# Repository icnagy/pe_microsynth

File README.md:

# PE Microsynth / Clef B30

Redrawn in KiCad.

Practical Electronics June 1982
MICROSYNTH Part 1 by A.R. Bradford MSc page 18

Practical Electronics July 1982
MICROSYNTH Part 2 by A.R. Bradford MSc page 38

Practical Electronics August 1982
MICROSYNTH Part 3 by A.R.Bradford MSc page 36

## Schematics

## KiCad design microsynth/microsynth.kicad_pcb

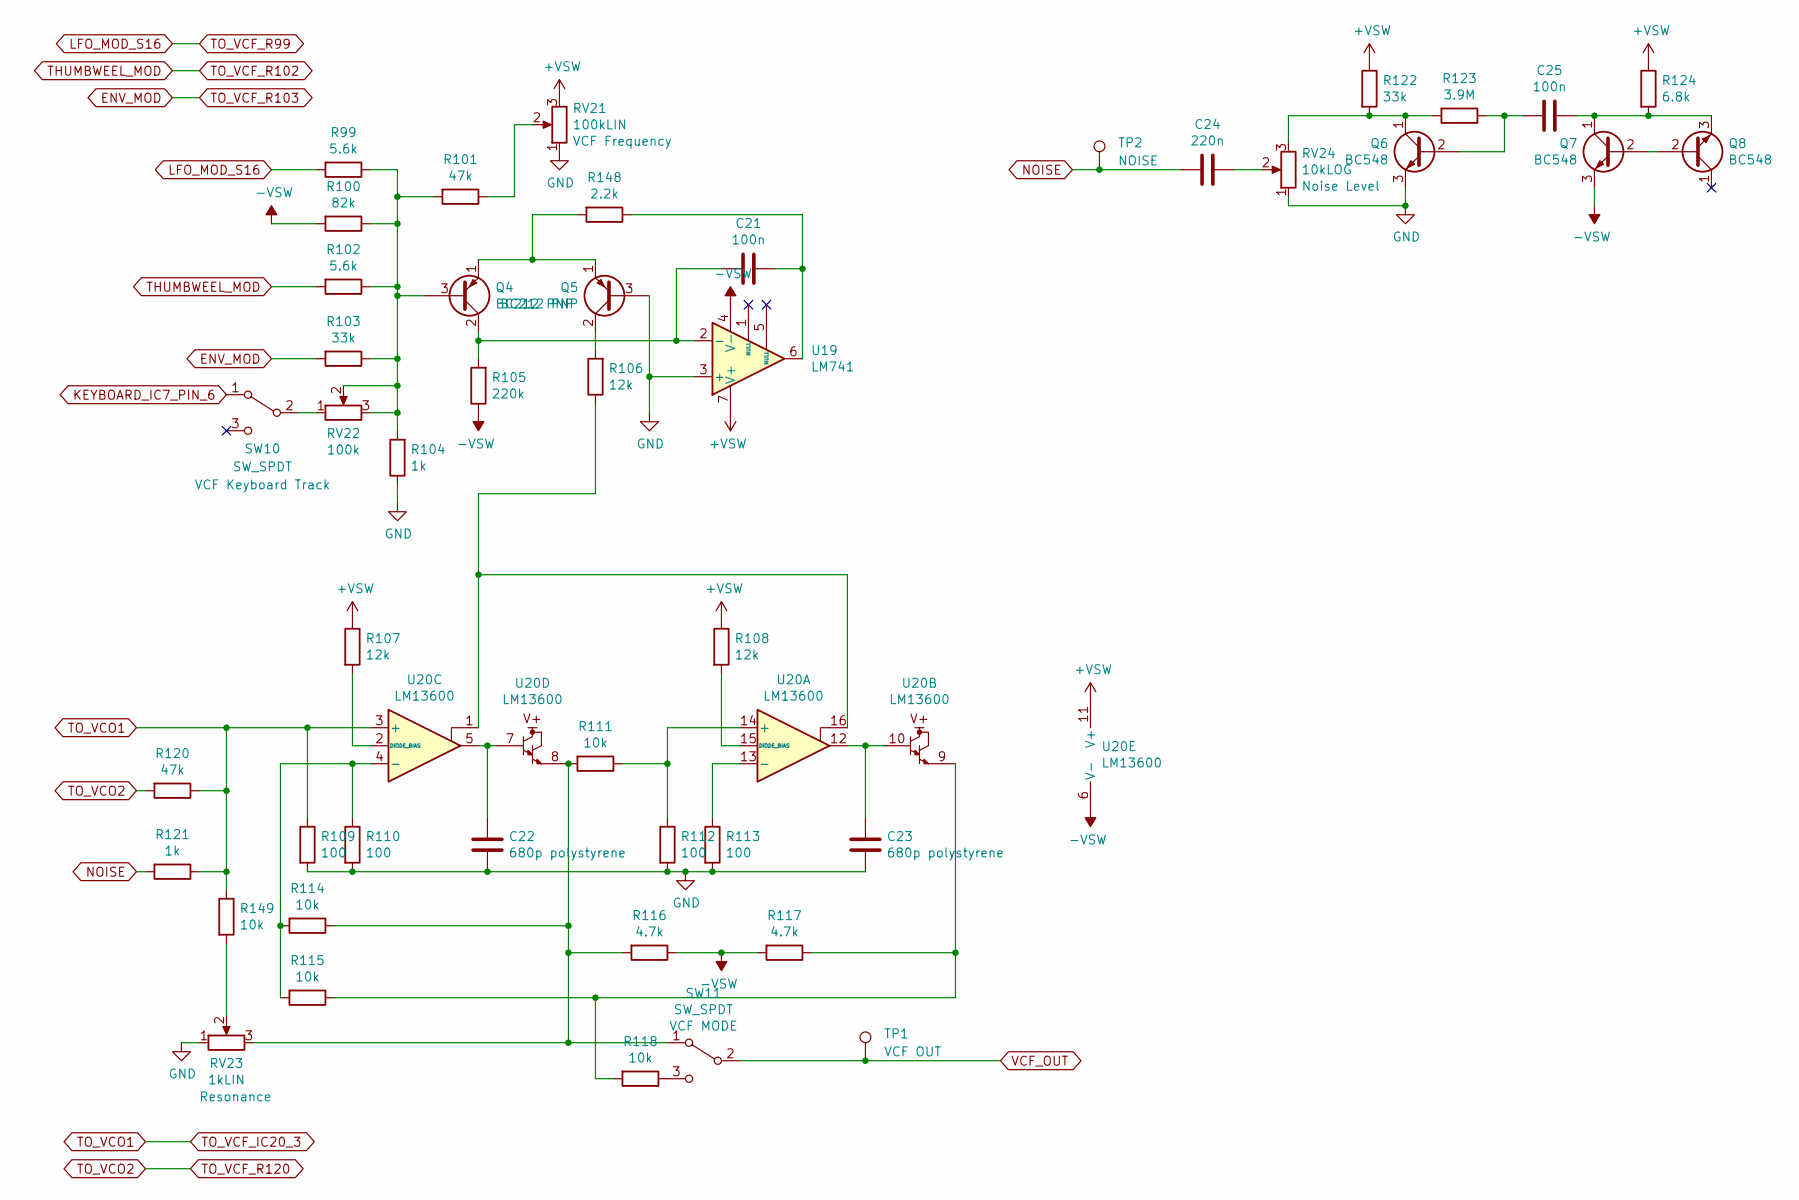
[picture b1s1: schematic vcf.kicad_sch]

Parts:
C21, C25: 100n; C_Rect_L7.2mm_W2.5mm_P5.00mm_FKS2_FKP2_MKS2_MKP2
C22, C23: 680p polystyrene; C_Axial_L12.0mm_D6.5mm_P15.00mm_Horizontal
C24: 220n; C_Rect_L7.2mm_W2.5mm_P5.00mm_FKS2_FKP2_MKS2_MKP2
Q4, Q5: BC212 PNP; TO-92L_Inline_Wide
Q6, Q7, Q8: BC548; TO-92L_Inline_Wide
R99, R102: 5.6k; R_Axial_DIN0207_L6.3mm_D2.5mm_P10.16mm_Horizontal
R100: 82k; R_Axial_DIN0207_L6.3mm_D2.5mm_P10.16mm_Horizontal
R101, R120: 47k; R_Axial_DIN0207_L6.3mm_D2.5mm_P10.16mm_Horizontal
R103, R122: 33k; R_Axial_DIN0207_L6.3mm_D2.5mm_P10.16mm_Horizontal
R104, R121: 1k; R_Axial_DIN0207_L6.3mm_D2.5mm_P10.16mm_Horizontal
R105: 220k; R_Axial_DIN0207_L6.3mm_D2.5mm_P10.16mm_Horizontal
R106, R107, R108: 12k; R_Axial_DIN0207_L6.3mm_D2.5mm_P10.16mm_Horizontal
R109, R110, R112, R113: 100; R_Axial_DIN0207_L6.3mm_D2.5mm_P10.16mm_Horizontal
R111, R114, R115, R118, R149: 10k; R_Axial_DIN0207_L6.3mm_D2.5mm_P10.16mm_Horizontal
R116, R117: 4.7k; R_Axial_DIN0207_L6.3mm_D2.5mm_P10.16mm_Horizontal
R123: 3.9M; R_Axial_DIN0207_L6.3mm_D2.5mm_P10.16mm_Horizontal
R124: 6.8k; R_Axial_DIN0207_L6.3mm_D2.5mm_P10.16mm_Horizontal
R148: 2.2k; R_Axial_DIN0207_L6.3mm_D2.5mm_P10.16mm_Horizontal
RV21: 100kLIN; Pot_16mm_NoDet_RV16AF-4A
RV22: 100k; Potentiometer_Bourns_3296W_Vertical
RV23: 1kLIN; Pot_16mm_NoDet_RV16AF-4A
RV24: 10kLOG; Pot_16mm_NoDet_RV16AF-4A
SW10, SW11: SW_SPDT; 11-SS-22-701C
TP1: VCF OUT; TestPoint_Pad_D2.0mm
TP2: NOISE; TestPoint_Pad_D2.0mm
U19: LM741; DIP-8_W7.62mm_LongPads
U20: LM13600; DIP-16_W7.62mm_LongPads

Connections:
+VSW: R107.1, R108.1, R122.1, R124.1, RV21.3, U19.7 (V+), U20.11 (V+); also elsewhere on the board
-VSW: Q7.3 (E), R100.2, R105.1, R116.1, R117.2, U19.4 (V-), U20.6 (V-); also elsewhere on the board
ENV_MOD: R103.2; also elsewhere on the board
GND: C22.2, C23.2, Q5.3 (B), Q6.3 (E), R104.1, R109.2, R110.2, R112.2, R113.2, RV21.1, RV23.1, RV24.1, U19.3 (+); also elsewhere on the board
KEYBOARD_IC7_PIN_6: SW10.1 (A); also elsewhere on the board
LFO_MOD_S16: R99.2; also elsewhere on the board
NOISE: C24.2, R121.2, TP2.1
unnamed: C21.1, R148.1, U19.6
unnamed: C21.2, Q4.2 (C), R105.2, U19.2 (-)
unnamed: C22.1, U20.5, U20.7
unnamed: C23.1, U20.10, U20.12
unnamed: C24.1, RV24.2
unnamed: C25.1, Q7.1 (C), Q8.3 (E), R124.2
unnamed: C25.2, Q6.2 (B), R123.1
unnamed: Q4.1 (E), Q5.1 (E), R148.2
unnamed: Q4.3 (B), R99.1, R100.1, R101.2, R102.1, R103.1, R104.2, RV22.2, RV22.3
unnamed: Q5.2 (C), R106.2
unnamed: Q6.1 (C), R122.2, R123.2, RV24.3
unnamed: Q7.2 (B), Q8.2 (B)
unnamed: R101.1, RV21.2
unnamed: R106.1, U20.1, U20.16
unnamed: R107.2, U20.2 (DIODE_BIAS)
unnamed: R108.2, U20.15 (DIODE_BIAS)
unnamed: R110.1, R114.2, R115.2, U20.4 (-)
unnamed: R111.1, R112.1, U20.14 (+)
unnamed: R111.2, R114.1, R116.2, RV23.3, SW11.1 (A), U20.8
unnamed: R113.1, U20.13 (-)
unnamed: R115.1, R117.1, R118.2, U20.9
unnamed: R118.1, SW11.3 (C)
unnamed: R149.2, RV23.2
unnamed: RV22.1, SW10.2 (B)
THUMBWEEL_MOD: R102.2; also elsewhere on the board
TO_VCF_IC20_3: R109.1, R120.1, R121.1, R149.1, U20.3 (+); also elsewhere on the board
TO_VCF_R120: R120.2; also elsewhere on the board
VCF_OUT: SW11.2 (B), TP1.1; also elsewhere on the board

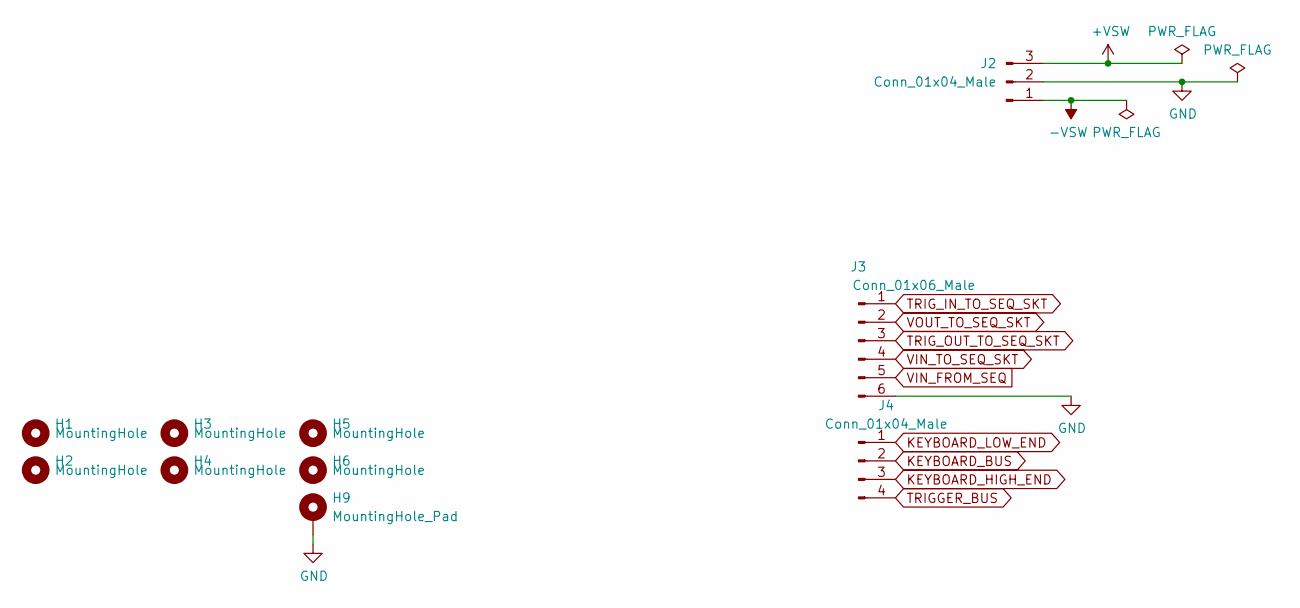
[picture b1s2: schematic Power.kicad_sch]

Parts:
H1, H2, H3, H4, H5, H6: MountingHole; MountingHole_3.2mm_M3
H9: MountingHole_Pad; PinHeader_1x01_P2.54mm_Vertical
J2: Conn_01x04_Male; PhoenixContact_MSTBA_2,5_3-G_1x03_P5.00mm_Horizontal
J3: Conn_01x06_Male; PinHeader_1x06_P2.54mm_Vertical
J4: Conn_01x04_Male; PinHeader_1x04_P2.54mm_Vertical

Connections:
+VSW: J2.3; also elsewhere on the board
-VSW: J2.1; also elsewhere on the board
GND: H9.1, J2.2, J3.6; also elsewhere on the board
KEYBOARD_BUS: J4.2; also elsewhere on the board
KEYBOARD_HIGH_END: J4.3; also elsewhere on the board
KEYBOARD_LOW_END: J4.1; also elsewhere on the board
TRIGGER_BUS: J4.4; also elsewhere on the board
TRIG_IN_TO_SEQ_SKT: J3.1; also elsewhere on the board
TRIG_OUT_TO_SEQ_SKT: J3.3; also elsewhere on the board
VIN_FROM_SEQ: J3.5; also elsewhere on the board
VIN_TO_SEQ_SKT: J3.4; also elsewhere on the board
VOUT_TO_SEQ_SKT: J3.2; also elsewhere on the board

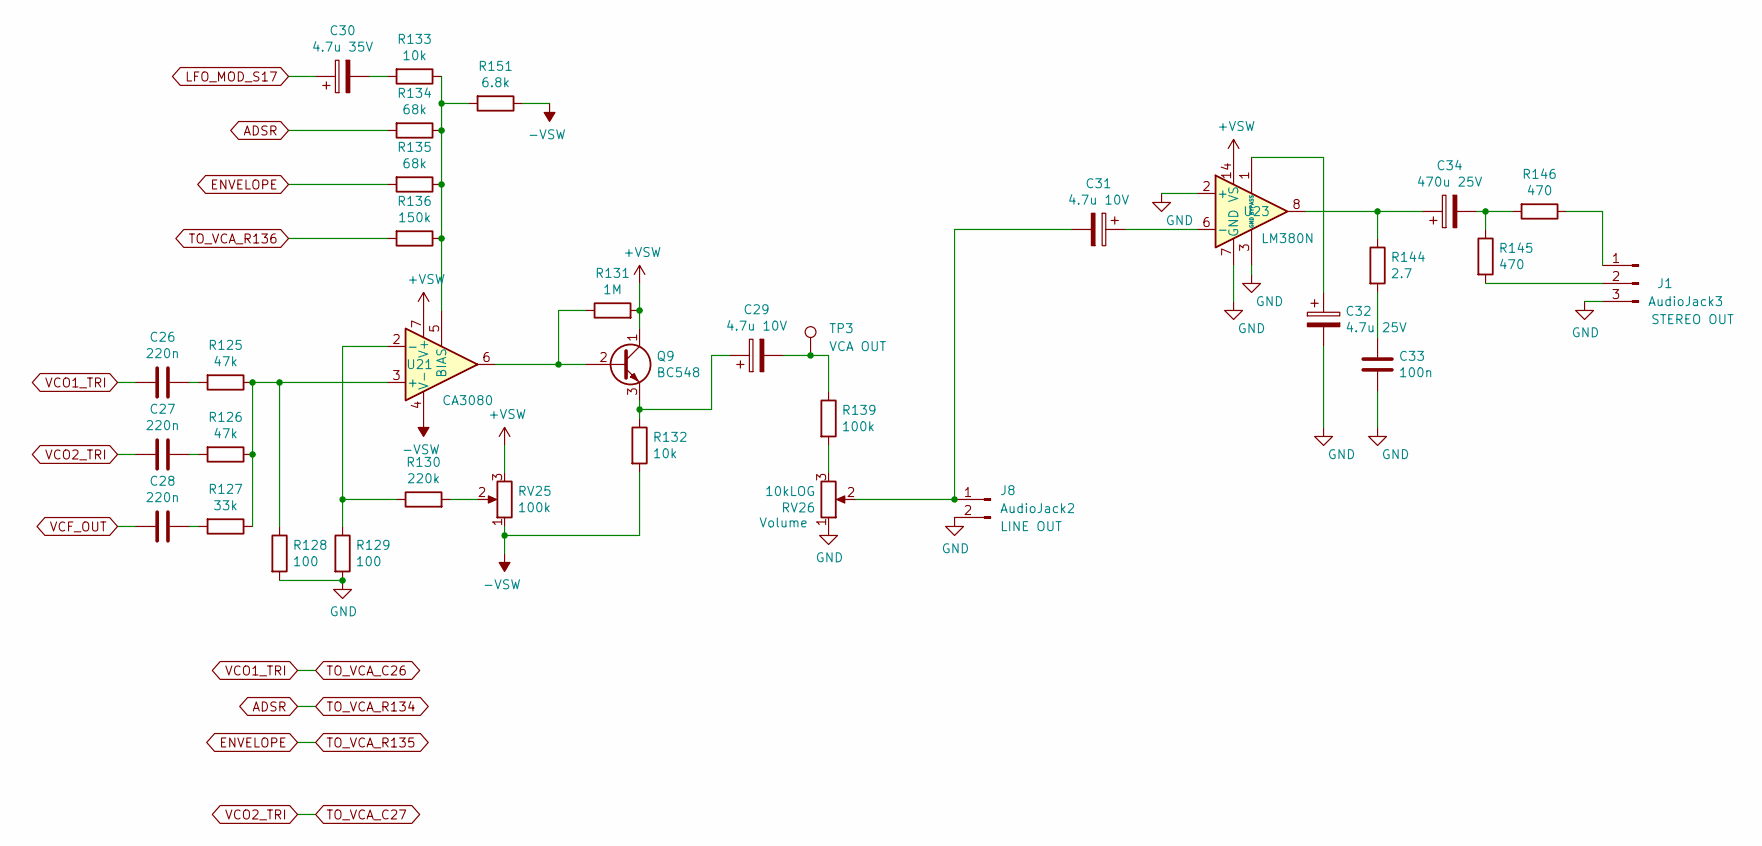
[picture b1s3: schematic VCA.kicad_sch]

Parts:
C26, C27, C28: 220n; C_Rect_L7.2mm_W2.5mm_P5.00mm_FKS2_FKP2_MKS2_MKP2
C29, C31: 4.7u 10V; CP_Radial_D5.0mm_P2.50mm
C30: 4.7u 35V; CP_Radial_D5.0mm_P2.50mm
C32: 4.7u 25V; CP_Radial_D5.0mm_P2.50mm
C33: 100n; C_Rect_L7.2mm_W2.5mm_P5.00mm_FKS2_FKP2_MKS2_MKP2
C34: 470u 25V; CP_Radial_D10.0mm_P5.00mm
J1: AudioJack3; PinHeader_1x03_P2.54mm_Vertical
J8: AudioJack2; PinHeader_1x02_P2.54mm_Vertical
Q9: BC548; TO-92L_Inline_Wide
R125, R126: 47k; R_Axial_DIN0207_L6.3mm_D2.5mm_P10.16mm_Horizontal
R127: 33k; R_Axial_DIN0207_L6.3mm_D2.5mm_P10.16mm_Horizontal
R128, R129: 100; R_Axial_DIN0207_L6.3mm_D2.5mm_P10.16mm_Horizontal
R130: 220k; R_Axial_DIN0207_L6.3mm_D2.5mm_P10.16mm_Horizontal
R131: 1M; R_Axial_DIN0207_L6.3mm_D2.5mm_P10.16mm_Horizontal
R132, R133: 10k; R_Axial_DIN0207_L6.3mm_D2.5mm_P10.16mm_Horizontal
R134, R135: 68k; R_Axial_DIN0207_L6.3mm_D2.5mm_P10.16mm_Horizontal
R136: 150k; R_Axial_DIN0207_L6.3mm_D2.5mm_P10.16mm_Horizontal
R139: 100k; R_Axial_DIN0207_L6.3mm_D2.5mm_P10.16mm_Horizontal
R144: 2.7; R_Axial_DIN0207_L6.3mm_D2.5mm_P10.16mm_Horizontal
R145, R146: 470; R_Axial_DIN0207_L6.3mm_D2.5mm_P10.16mm_Horizontal
R151: 6.8k; R_Axial_DIN0207_L6.3mm_D2.5mm_P10.16mm_Horizontal
RV25: 100k; Potentiometer_Bourns_3296W_Vertical
RV26: 10kLOG; PinHeader_1x03_P2.54mm_Vertical
TP3: VCA OUT; TestPoint_Pad_D2.0mm
U21: CA3080; DIP-8_W7.62mm_LongPads
U23: LM380N; DIP-14_W7.62mm_LongPads

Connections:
+VSW: Q9.1 (C), R131.2, RV25.3, U21.7 (V+), U23.14 (VS); also elsewhere on the board
-VSW: R132.2, R151.1, RV25.1, U21.4 (V-); also elsewhere on the board
ADSR: R134.2; also elsewhere on the board
ENVELOPE: R135.2; also elsewhere on the board
GND: C32.2, C33.2, J1.3, J8.2, R128.2, R129.2, RV26.1, U23.2 (+), U23.3 (GND), U23.4 (GND), U23.5 (GND), U23.7 (GND), U23.10 (GND), U23.11 (GND), U23.12 (GND); also elsewhere on the board
LFO_MOD_S17: C30.1; also elsewhere on the board
unnamed: C26.1, R125.2
unnamed: C27.2, R126.2
unnamed: C28.2, R127.2
unnamed: C29.1, Q9.3 (E), R132.1
unnamed: C29.2, R139.1, TP3.1
unnamed: C30.2, R133.2
unnamed: C31.1, U23.6 (-)
unnamed: C31.2, J8.1, RV26.2
unnamed: C32.1, U23.1 (BYPASS)
unnamed: C33.1, R144.2
unnamed: C34.1, R144.1, U23.8
unnamed: C34.2, R145.1, R146.2
unnamed: J1.1, R146.1
unnamed: J1.2, R145.2
unnamed: Q9.2 (B), R131.1, U21.6
unnamed: R125.1, R126.1, R127.1, R128.1, U21.3 (+)
unnamed: R129.1, R130.1, U21.2 (-)
unnamed: R130.2, RV25.2
unnamed: R133.1, R134.1, R135.1, R136.1, R151.2, U21.5 (BIAS)
unnamed: R139.2, RV26.3
TO_VCA_C26: C26.2; also elsewhere on the board
TO_VCA_C27: C27.1; also elsewhere on the board
TO_VCA_R136: R136.2; also elsewhere on the board
VCF_OUT: C28.1; also elsewhere on the board

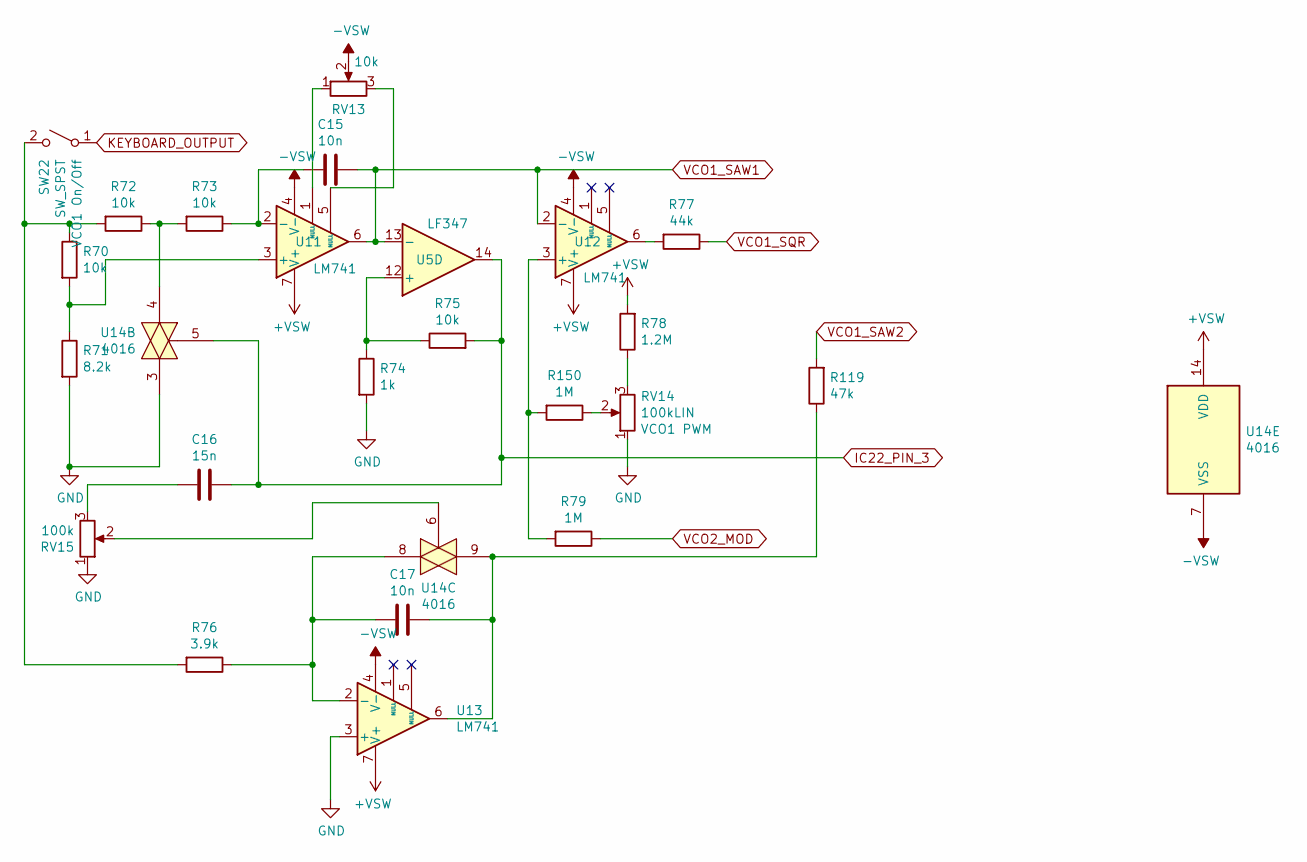
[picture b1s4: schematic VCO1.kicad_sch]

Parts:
C15, C17: 10n; C_Rect_L7.2mm_W2.5mm_P5.00mm_FKS2_FKP2_MKS2_MKP2
C16: 15n; C_Rect_L7.2mm_W3.5mm_P5.00mm_FKS2_FKP2_MKS2_MKP2
R70, R72, R73, R75: 10k; R_Axial_DIN0207_L6.3mm_D2.5mm_P10.16mm_Horizontal
R71: 8.2k; R_Axial_DIN0207_L6.3mm_D2.5mm_P10.16mm_Horizontal
R74: 1k; R_Axial_DIN0207_L6.3mm_D2.5mm_P10.16mm_Horizontal
R76: 3.9k; R_Axial_DIN0207_L6.3mm_D2.5mm_P10.16mm_Horizontal
R77: 44k; R_Axial_DIN0207_L6.3mm_D2.5mm_P10.16mm_Horizontal
R78: 1.2M; R_Axial_DIN0207_L6.3mm_D2.5mm_P10.16mm_Horizontal
R79, R150: 1M; R_Axial_DIN0207_L6.3mm_D2.5mm_P10.16mm_Horizontal
R119: 47k; R_Axial_DIN0207_L6.3mm_D2.5mm_P10.16mm_Horizontal
RV13: 10k; Potentiometer_Bourns_3296W_Vertical
RV14: 100kLIN; Pot_16mm_NoDet_RV16AF-4A
RV15: 100k; Potentiometer_Bourns_3296W_Vertical
SW22: SW_SPST; SPDT_KIT
U5: LF347; DIP-14_W7.62mm_LongPads
U11, U12, U13: LM741; DIP-8_W7.62mm_LongPads
U14: 4016; DIP-14_W7.62mm_LongPads

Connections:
+VSW: R78.2, U11.7 (V+), U12.7 (V+), U13.7 (V+), U14.14 (VDD); also elsewhere on the board
-VSW: RV13.2, U11.4 (V-), U12.4 (V-), U13.4 (V-), U14.7 (VSS); also elsewhere on the board
GND: R71.2, R74.2, RV14.1, RV15.1, U13.3 (+), U14.3; also elsewhere on the board
IC22_PIN_3: C16.1, R75.2, U5.14, U14.5; also elsewhere on the board
KEYBOARD_IC7_PIN_6: SW22.1 (A); also elsewhere on the board
unnamed: C15.2, R73.1, U11.2 (-)
unnamed: C16.2, RV15.3
unnamed: C17.1, R119.1, U13.6, U14.9
unnamed: C17.2, R76.1, U13.2 (-), U14.8
unnamed: R70.1, R72.2, R76.2, SW22.2 (B)
unnamed: R70.2, R71.1, U11.3 (+)
unnamed: R72.1, R73.2, U14.4
unnamed: R74.1, R75.1, U5.12 (+)
unnamed: R77.2, U12.6
unnamed: R78.1, RV14.3
unnamed: R150.1, RV14.2
unnamed: R79.2, R150.2, U12.3 (+)
unnamed: RV13.1, U11.1 (NULL)
unnamed: RV13.3, U11.5 (NULL)
unnamed: RV15.2, U14.6
TO_VCO1_R79: R79.1; also elsewhere on the board
VCO1_SAW1: C15.1, U5.13 (-), U11.6, U12.2 (-); also elsewhere on the board
VCO1_SAW2: R119.2; also elsewhere on the board
VCO1_SQR: R77.1; also elsewhere on the board

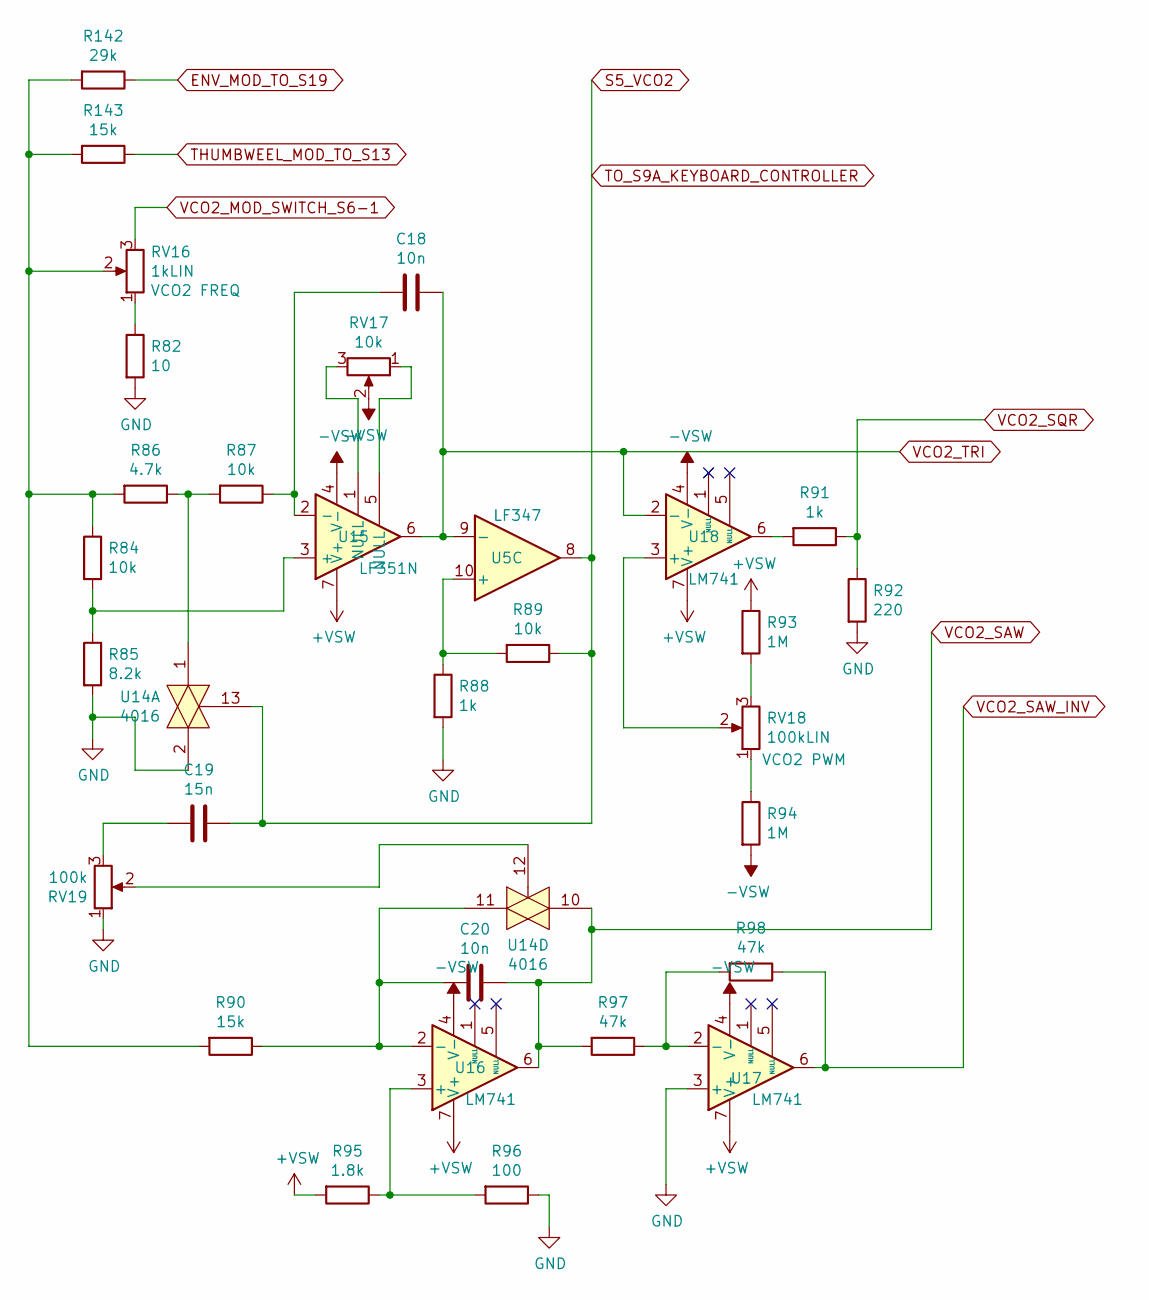
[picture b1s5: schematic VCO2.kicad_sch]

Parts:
C18, C20: 10n; C_Rect_L7.2mm_W2.5mm_P5.00mm_FKS2_FKP2_MKS2_MKP2
C19: 15n; C_Rect_L7.2mm_W3.5mm_P5.00mm_FKS2_FKP2_MKS2_MKP2
R82: 10; R_Axial_DIN0207_L6.3mm_D2.5mm_P10.16mm_Horizontal
R84, R87, R89: 10k; R_Axial_DIN0207_L6.3mm_D2.5mm_P10.16mm_Horizontal
R85: 8.2k; R_Axial_DIN0207_L6.3mm_D2.5mm_P10.16mm_Horizontal
R86: 4.7k; R_Axial_DIN0207_L6.3mm_D2.5mm_P10.16mm_Horizontal
R88, R91: 1k; R_Axial_DIN0207_L6.3mm_D2.5mm_P10.16mm_Horizontal
R90, R143: 15k; R_Axial_DIN0207_L6.3mm_D2.5mm_P10.16mm_Horizontal
R92: 220; R_Axial_DIN0207_L6.3mm_D2.5mm_P10.16mm_Horizontal
R93, R94: 1M; R_Axial_DIN0207_L6.3mm_D2.5mm_P10.16mm_Horizontal
R95: 1.8k; R_Axial_DIN0207_L6.3mm_D2.5mm_P10.16mm_Horizontal
R96: 100; R_Axial_DIN0207_L6.3mm_D2.5mm_P10.16mm_Horizontal
R97, R98: 47k; R_Axial_DIN0207_L6.3mm_D2.5mm_P10.16mm_Horizontal
R142: 29k; R_Axial_DIN0207_L6.3mm_D2.5mm_P10.16mm_Horizontal
RV16: 1kLIN; Pot_16mm_NoDet_RV16AF-4A
RV17: 10k; Potentiometer_Bourns_3296W_Vertical
RV18: 100kLIN; Pot_16mm_NoDet_RV16AF-4A
RV19: 100k; Potentiometer_Bourns_3296W_Vertical
U5: LF347; DIP-14_W7.62mm_LongPads
U14: 4016; DIP-14_W7.62mm_LongPads
U15: LF351N; DIP-8_W7.62mm_LongPads
U16, U17, U18: LM741; DIP-8_W7.62mm_LongPads

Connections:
+VSW: R93.1, R95.2, U15.7 (V+), U16.7 (V+), U17.7 (V+), U18.7 (V+); also elsewhere on the board
-VSW: R94.2, RV17.2, U15.4 (V-), U16.4 (V-), U17.4 (V-), U18.4 (V-); also elsewhere on the board
ENV_MOD_TO_S19: R142.1; also elsewhere on the board
GND: R82.2, R85.2, R88.2, R92.2, R96.1, RV19.1, U14.2, U17.3 (+); also elsewhere on the board
unnamed: C18.2, R87.1, U15.2 (-)
unnamed: C19.2, RV19.3
unnamed: C20.2, R90.1, U14.11, U16.2 (-)
unnamed: R82.1, RV16.1
unnamed: R84.2, R85.1, U15.3 (+)
unnamed: R86.1, R87.2, U14.1
unnamed: R88.1, R89.2, U5.10 (+)
unnamed: R91.2, U18.6
unnamed: R93.2, RV18.3
unnamed: R94.1, RV18.1
unnamed: R95.1, R96.2, U16.3 (+)
unnamed: R97.1, R98.2, U17.2 (-)
unnamed: R84.1, R86.2, R90.2, R142.2, R143.2, RV16.2
unnamed: RV17.1, U15.5 (NULL)
unnamed: RV17.3, U15.1 (NULL)
unnamed: RV18.2, U18.3 (+)
unnamed: RV19.2, U14.12
S5_VCO2: C19.1, R89.1, U5.8, U14.13; also elsewhere on the board
THUMBWEEL_MOD_TO_S13: R143.1; also elsewhere on the board
TO_VCA_C27: C18.1, U5.9 (-), U15.6, U18.2 (-); also elsewhere on the board
VCO2_MOD_SWITCH_S6-1: RV16.3; also elsewhere on the board
VCO2_SAW: C20.1, R97.2, U14.10, U16.6; also elsewhere on the board
VCO2_SAW_INV: R98.1, U17.6; also elsewhere on the board
VCO2_SQR: R91.1, R92.1; also elsewhere on the board

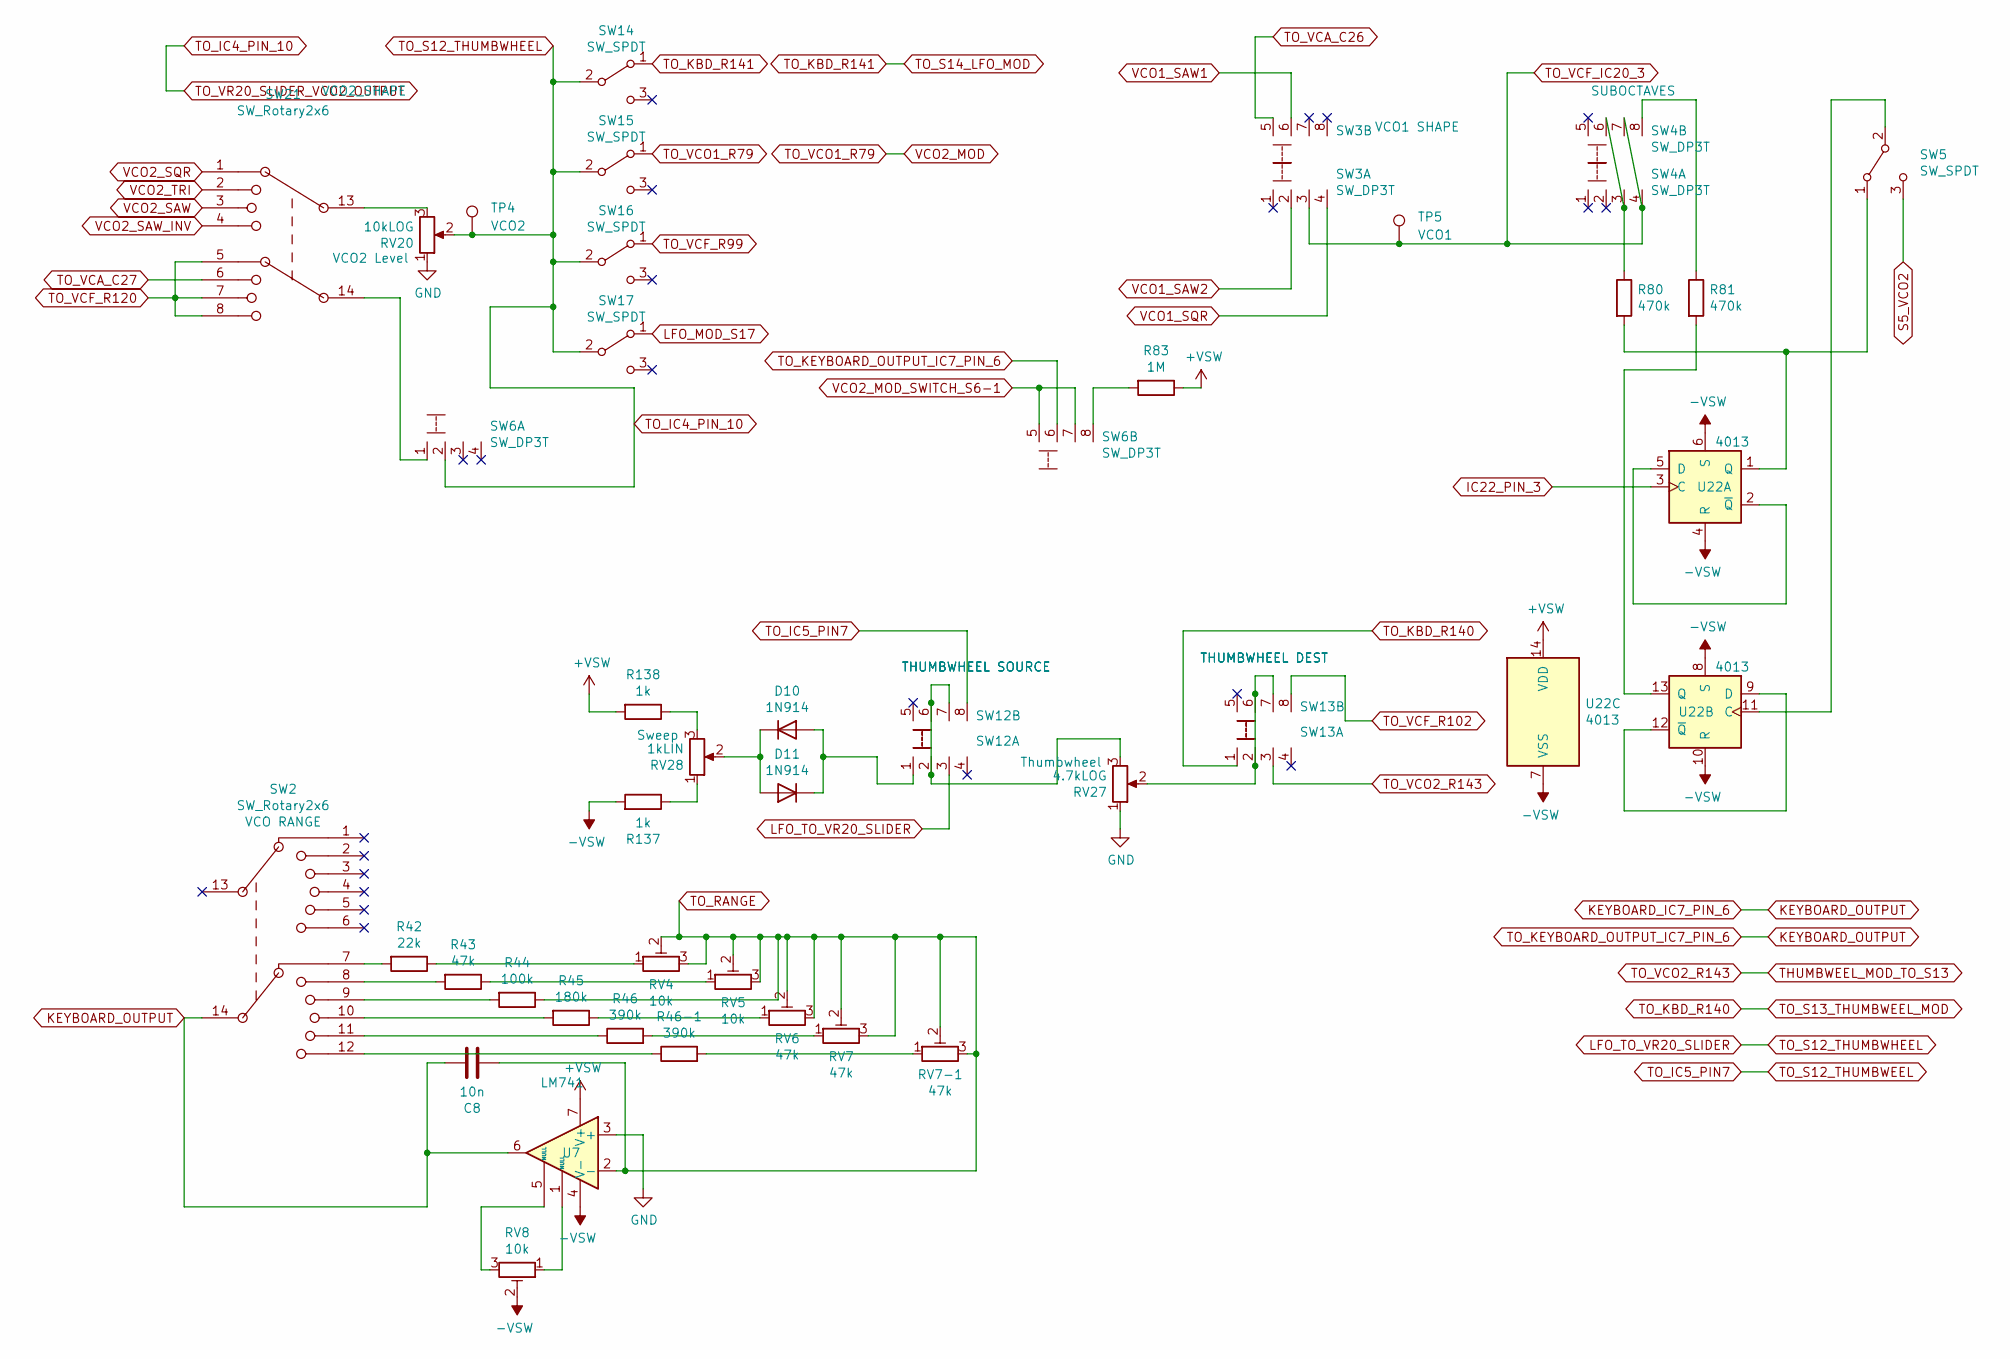
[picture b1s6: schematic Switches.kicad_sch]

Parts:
C8: 10n; C_Rect_L7.2mm_W2.5mm_P5.00mm_FKS2_FKP2_MKS2_MKP2
D10, D11: 1N914; D_DO-35_SOD27_P7.62mm_Horizontal
R42: 22k; R_Axial_DIN0207_L6.3mm_D2.5mm_P10.16mm_Horizontal
R43: 47k; R_Axial_DIN0207_L6.3mm_D2.5mm_P10.16mm_Horizontal
R44: 100k; R_Axial_DIN0207_L6.3mm_D2.5mm_P10.16mm_Horizontal
R45: 180k; R_Axial_DIN0207_L6.3mm_D2.5mm_P10.16mm_Horizontal
R46, R46-1: 390k; R_Axial_DIN0207_L6.3mm_D2.5mm_P10.16mm_Horizontal
R80, R81: 470k; R_Axial_DIN0207_L6.3mm_D2.5mm_P10.16mm_Horizontal
R83: 1M; R_Axial_DIN0207_L6.3mm_D2.5mm_P10.16mm_Horizontal
R137, R138: 1k; R_Axial_DIN0207_L6.3mm_D2.5mm_P10.16mm_Horizontal
RV4, RV5, RV8: 10k; Potentiometer_Bourns_3296W_Vertical
RV6, RV7, RV7-1: 47k; Potentiometer_Bourns_3296W_Vertical
RV20: 10kLOG; Pot_16mm_NoDet_RV16AF-4A
RV27: 4.7kLOG; Potentiometer_Bourns_PTV09A-2_Vertical
RV28: 1kLIN; Pot_16mm_NoDet_RV16AF-4A
SW2: SW_Rotary2x6; SR2511F-0206-(L)K0A-C9-S-3
SW3, SW4, SW6: SW_DP3T; 11-SS-23-832C
SW5, SW14, SW15, SW16, SW17: SW_SPDT; 11-SS-22-701C
SW12: THUMBWHEEL SOURCE; 11-SS-23-832C
SW13: THUMBWHEEL DEST; 11-SS-23-832C
SW21: SW_Rotary2x6; SR2511F-0204-(L)K0A-C9-S-3
TP4: VCO2; TestPoint_Pad_D2.0mm
TP5: VCO1; TestPoint_Pad_D2.0mm
U7: LM741; DIP-8_W7.62mm_LongPads
U22: 4013; DIP-14_W7.62mm_LongPads

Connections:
+VSW: R83.1, R138.2, U7.7 (V+), U22.14 (VDD); also elsewhere on the board
-VSW: R137.2, RV8.2, U7.4 (V-), U22.4 (R), U22.6 (S), U22.7 (VSS), U22.8 (S), U22.10 (R); also elsewhere on the board
GND: RV20.1, RV27.1, U7.3 (+); also elsewhere on the board
IC22_PIN_3: U22.3 (C); also elsewhere on the board
KEYBOARD_IC7_PIN_6: C8.1, SW2.14, SW6.6, U7.6; also elsewhere on the board
LFO_MOD_S16: SW16.1 (A); also elsewhere on the board
LFO_MOD_S17: SW17.1 (A); also elsewhere on the board
LFO_TO_VR20_SLIDER: RV20.2, SW6.2, SW12.3, SW14.2 (B), SW15.2 (B), SW16.2 (B), SW17.2 (B), TP4.1; also elsewhere on the board
unnamed: D10.1 (K), D11.2 (A), RV28.2
unnamed: D10.2 (A), D11.1 (K), SW12.1
unnamed: R42.1, RV4.1
unnamed: R42.2, SW2.7
unnamed: R43.1, RV5.1
unnamed: R43.2, SW2.8
unnamed: R44.2, SW2.9
unnamed: R45.1, RV6.1
unnamed: R45.2, SW2.10
unnamed: R46-1.1, SW2.12
unnamed: R46-1.2, RV7-1.1
unnamed: R46.1, SW2.11
unnamed: R46.2, RV7.1
unnamed: R80.1, SW4.3, SW4.6
unnamed: R80.2, SW5.1 (A), U22.1 (Q)
unnamed: R81.1, SW4.8
unnamed: R81.2, U22.13 (Q)
unnamed: R83.2, SW6.8
unnamed: R137.1, RV28.1
unnamed: R138.1, RV28.3
unnamed: RV8.1, U7.1 (NULL)
unnamed: RV8.3, U7.5 (NULL)
unnamed: RV20.3, SW21.13
unnamed: RV27.2, SW13.2, SW13.6, SW13.7
unnamed: RV27.3, SW12.2, SW12.6, SW12.7
unnamed: SW5.2 (B), U22.11 (C)
unnamed: SW6.1, SW21.14
unnamed: U22.2 (~Q), U22.5 (D)
unnamed: U22.9 (D), U22.12 (~Q)
S5_VCO2: SW5.3 (C); also elsewhere on the board
THUMBWEEL_MOD: SW13.8; also elsewhere on the board
THUMBWEEL_MOD_TO_S13: SW13.3; also elsewhere on the board
TO_IC5_PIN7: SW12.8; also elsewhere on the board
TO_KBD_R140: SW13.1; also elsewhere on the board
TO_KBD_R141: SW14.1 (A); also elsewhere on the board
TO_RANGE: C8.2, R44.1, RV4.2, RV4.3, RV5.2, RV5.3, RV6.2, RV6.3, RV7.2, RV7.3, RV7-1.2, RV7-1.3, U7.2 (-); also elsewhere on the board
TO_VCA_C26: SW3.5; also elsewhere on the board
TO_VCA_C27: SW21.2, SW21.6; also elsewhere on the board
TO_VCF_IC20_3: SW3.3, SW4.4, SW4.7, TP5.1; also elsewhere on the board
TO_VCF_R120: SW21.5, SW21.7, SW21.8; also elsewhere on the board
TO_VCO1_R79: SW15.1 (A); also elsewhere on the board
VCO1_SAW1: SW3.6; also elsewhere on the board
VCO1_SAW2: SW3.2; also elsewhere on the board
VCO1_SQR: SW3.4; also elsewhere on the board
VCO2_MOD_SWITCH_S6-1: SW6.5, SW6.7; also elsewhere on the board
VCO2_SAW: SW21.3; also elsewhere on the board
VCO2_SAW_INV: SW21.4; also elsewhere on the board
VCO2_SQR: SW21.1; also elsewhere on the board

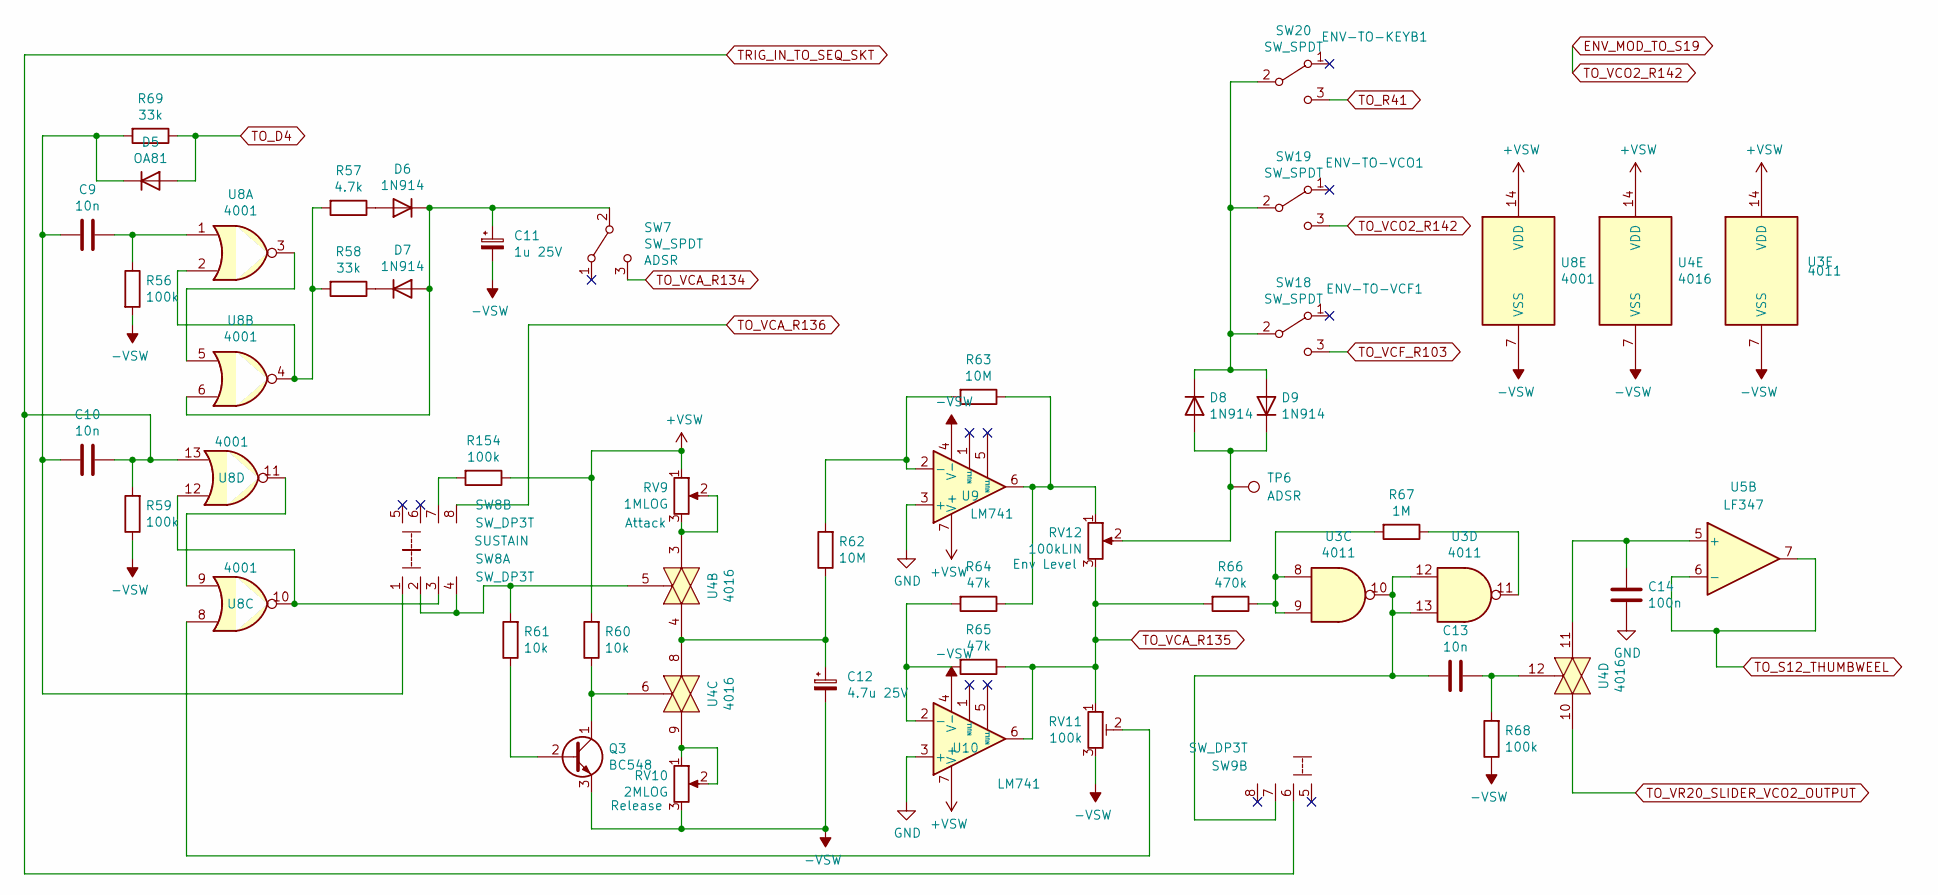
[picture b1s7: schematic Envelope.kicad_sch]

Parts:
C9, C10, C13: 10n; C_Rect_L7.2mm_W2.5mm_P5.00mm_FKS2_FKP2_MKS2_MKP2
C11: 1u 25V; CP_Radial_D5.0mm_P2.50mm
C12: 4.7u 25V; CP_Radial_D5.0mm_P2.50mm
C14: 100n; C_Rect_L7.2mm_W2.5mm_P5.00mm_FKS2_FKP2_MKS2_MKP2
D5: OA81; D_A-405_P10.16mm_Horizontal
D6, D7, D8, D9: 1N914; D_DO-35_SOD27_P7.62mm_Horizontal
Q3: BC548; TO-92L_Inline_Wide
R56, R59, R68, R154: 100k; R_Axial_DIN0207_L6.3mm_D2.5mm_P10.16mm_Horizontal
R57: 4.7k; R_Axial_DIN0207_L6.3mm_D2.5mm_P10.16mm_Horizontal
R58, R69: 33k; R_Axial_DIN0207_L6.3mm_D2.5mm_P10.16mm_Horizontal
R60, R61: 10k; R_Axial_DIN0207_L6.3mm_D2.5mm_P10.16mm_Horizontal
R62, R63: 10M; R_Axial_DIN0207_L6.3mm_D2.5mm_P10.16mm_Horizontal
R64, R65: 47k; R_Axial_DIN0207_L6.3mm_D2.5mm_P10.16mm_Horizontal
R66: 470k; R_Axial_DIN0207_L6.3mm_D2.5mm_P10.16mm_Horizontal
R67: 1M; R_Axial_DIN0207_L6.3mm_D2.5mm_P10.16mm_Horizontal
RV9: 1MLOG; Pot_16mm_NoDet_RV16AF-4A
RV10: 2MLOG; Pot_16mm_NoDet_RV16AF-4A
RV11: 100k; Potentiometer_Bourns_3296W_Vertical
RV12: 100kLIN; Pot_16mm_NoDet_RV16AF-4A
SW7, SW18, SW19, SW20: SW_SPDT; 11-SS-22-701C
SW8, SW9: SW_DP3T; 11-SS-23-832C
TP6: ADSR; TestPoint_Pad_D2.0mm
U3: 4011; DIP-14_W7.62mm_LongPads
U4: 4016; DIP-14_W7.62mm_LongPads
U5: LF347; DIP-14_W7.62mm_LongPads
U8: 4001; DIP-14_W7.62mm_LongPads
U9, U10: LM741; DIP-8_W7.62mm_LongPads

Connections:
+VSW: R60.2, R154.1, RV9.1, U3.14 (VDD), U4.14 (VDD), U8.14 (VDD), U9.7 (V+), U10.7 (V+); also elsewhere on the board
-VSW: C11.2, C12.2, Q3.3 (E), R56.2, R59.1, R68.1, RV10.3, RV11.3, U3.7 (VSS), U4.7 (VSS), U8.7 (VSS), U9.4 (V-), U10.4 (V-); also elsewhere on the board
ADSR: SW7.3 (C); also elsewhere on the board
ENVELOPE: R65.1, R66.2, RV11.1, RV12.3, U10.6; also elsewhere on the board
ENV_MOD: SW18.3 (C); also elsewhere on the board
ENV_MOD_TO_S19: SW19.3 (C); also elsewhere on the board
GND: C14.2, U9.3 (+), U10.3 (+); also elsewhere on the board
LFO_TO_VR20_SLIDER: U4.10; also elsewhere on the board
unnamed: C9.1, R56.1, U8.1
unnamed: C9.2, C10.2, D5.1 (K), R69.2, SW8.1
unnamed: C11.1, D6.1 (K), D7.2 (A), SW7.2 (B), U8.6
unnamed: C12.1, R62.1, U4.4, U4.8
unnamed: C13.1, R68.2, U4.12
unnamed: C13.2, SW9.7, U3.10, U3.12, U3.13
unnamed: C14.1, U4.11, U5.5 (+)
unnamed: D6.2 (A), R57.1
unnamed: D7.1 (K), R58.1
unnamed: D8.1 (K), D9.2 (A), SW18.2 (B), SW19.2 (B), SW20.2 (B)
unnamed: D8.2 (A), D9.1 (K), RV12.2, TP6.1
unnamed: Q3.1 (C), R60.1, U4.6
unnamed: Q3.2 (B), R61.1
unnamed: R57.2, R58.2, U8.2, U8.4
unnamed: R61.2, SW8.2, SW8.4, U4.5
unnamed: R62.2, R63.2, U9.2 (-)
unnamed: R63.1, R64.1, RV12.1, U9.6
unnamed: R64.2, R65.2, U10.2 (-)
unnamed: R66.1, R67.2, U3.8, U3.9
unnamed: R67.1, U3.11
unnamed: R154.2, SW8.7
unnamed: RV9.2, RV9.3, U4.3
unnamed: RV10.1, RV10.2, U4.9
unnamed: RV11.2, U8.8
unnamed: SW8.3, U8.10, U8.12
unnamed: U8.3, U8.5
unnamed: U8.9, U8.11
TO_D4: D5.2 (A), R69.1; also elsewhere on the board
TO_IC5_PIN7: U5.6 (-), U5.7; also elsewhere on the board
TO_R41: SW20.3 (C); also elsewhere on the board
TO_VCA_R136: SW8.8; also elsewhere on the board
TRIG_IN_TO_SEQ_SKT: C10.1, R59.2, SW9.6, U8.13; also elsewhere on the board
